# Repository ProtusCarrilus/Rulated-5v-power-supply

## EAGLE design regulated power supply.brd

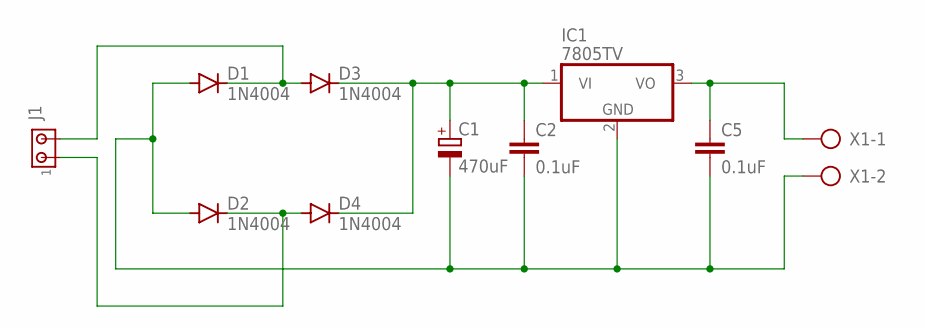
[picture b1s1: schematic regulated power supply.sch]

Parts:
C1: 470uF; E2,5-7
C2, C5: 0.1uF; C025-050X050
D1, D2, D3, D4: 1N4004; DO41-10
IC1: 7805TV; TO220V
J1: MTA02-100; 10X02MTA
X1: AK300/2

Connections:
unnamed: D1.C, D3.A, J1.2
unnamed: D2.C, D4.A, J1.1
unnamed: C1.+, C2.1, D3.C, D4.C, IC1.1 (VI)
unnamed: C1.-, C2.2, C5.2, D1.A, D2.A, IC1.2 (GND), X1.2
unnamed: C5.1, IC1.3 (VO), X1.1

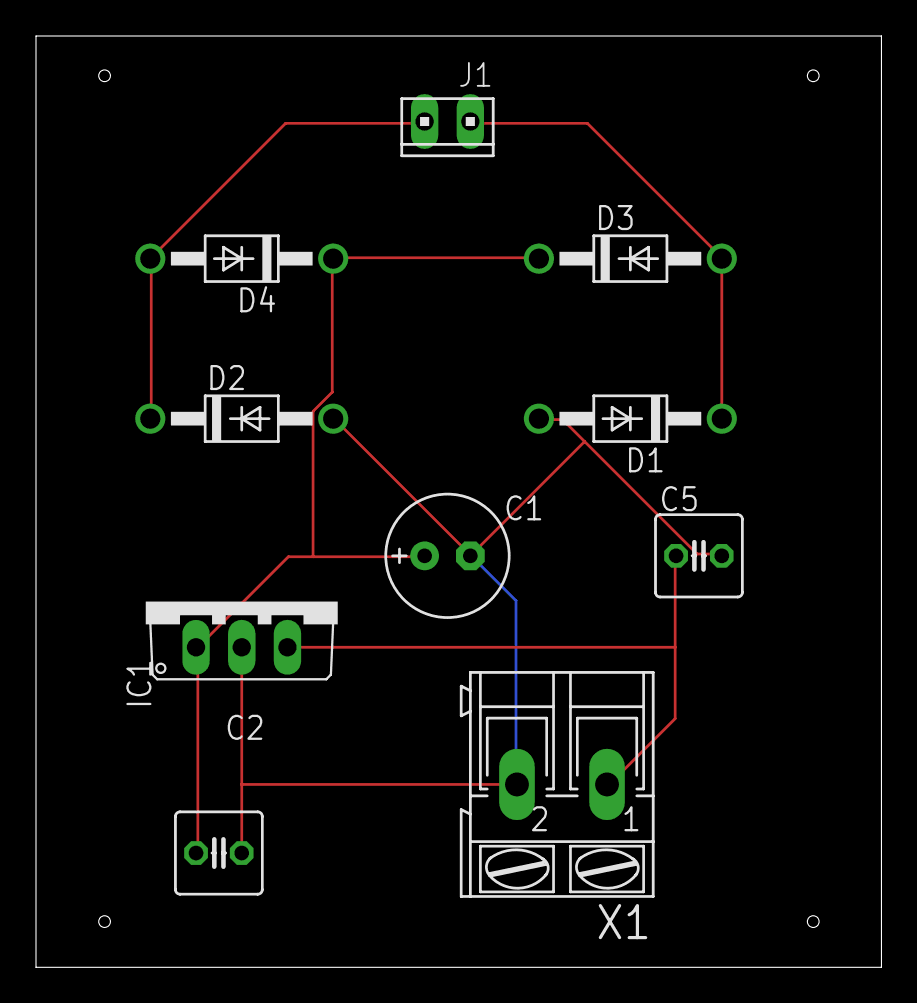
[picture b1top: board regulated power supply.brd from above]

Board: 2 copper layers, 47.0 x 51.7 mm, 10 parts (0 on the bottom side), 5 nets.
